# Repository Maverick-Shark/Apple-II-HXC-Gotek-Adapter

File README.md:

### Source

https://github.com/liveboxandy/Gotek-Rotary-Encoder

###  Description

Simple adapter PCB based on the wiring diagram from https://hxc2001.com/docs/gotek-floppy-emulator-hxc-firmware/pages/apple.html

### BOM

[Interactive BOM](https://djtersteegc.github.io/Apple-II-HXC-Gotek-Adapter/ibom.html)

| Item                                | Qty  | Notes                               | Link                                                         |
| ----------------------------------- | ---- | ----------------------------------- | ------------------------------------------------------------ |
| 2x17 34p 2.54mm Female Pin Socket   | 1    |                                     | [AliExpress](https://www.aliexpress.us/item/3256805948524386.html) |
| 2x10 20p 2.54mm IDC Male Box Header | 1    |                                     | [AliExpress](https://www.aliexpress.us/item/3256807284267150.html) |
| 1x4 4p 2.54mm Female Pin Socket     | 1    |                                     | [AliExpress](https://www.aliexpress.us/item/2255800509919410.html) |
| Female Dupont Jumper Wires          | 2    | From adapter to Gotek TX/RX headers | [AliExpress](https://www.aliexpress.us/item/3256807188673626.html) |
| 1x40 2.54mm Male Header             | 1    | To populate Gotek header pins       | [AliExpress](https://www.aliexpress.us/item/3256805949945647.html) |

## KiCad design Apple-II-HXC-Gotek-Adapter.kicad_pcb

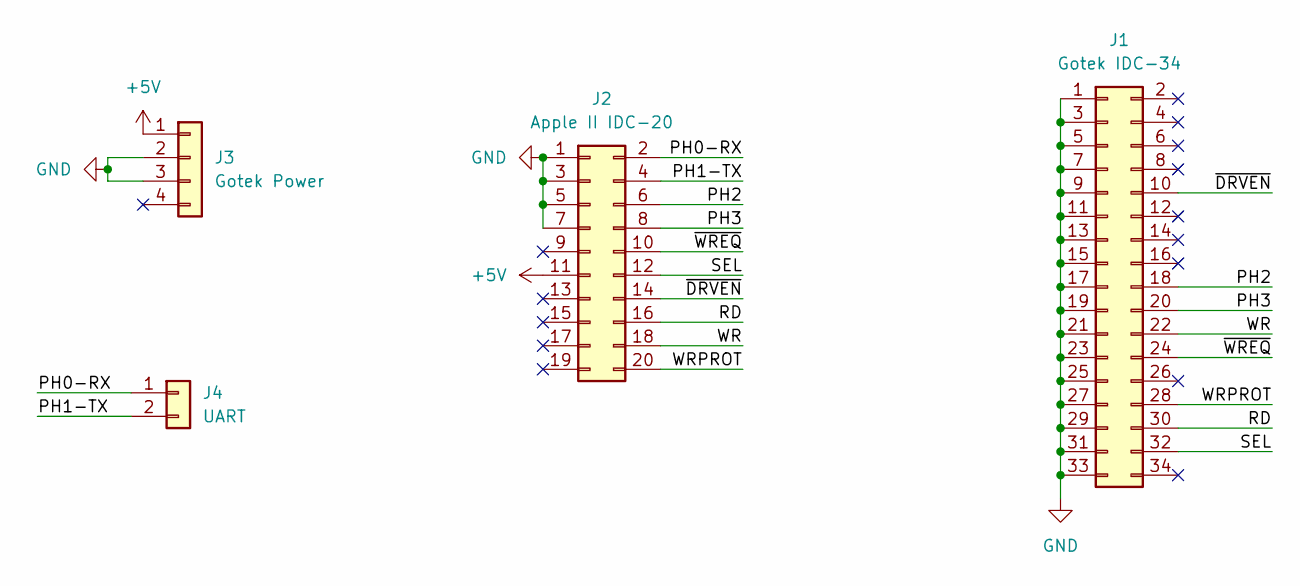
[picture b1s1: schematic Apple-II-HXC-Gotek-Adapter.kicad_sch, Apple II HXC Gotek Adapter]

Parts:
J1: Gotek IDC-34; PinSocket_2x17_P2.54mm_Vertical
J2: Apple II IDC-20; IDC-Header_2x10_P2.54mm_Vertical
J3: Gotek Power; PinSocket_1x04_P2.54mm_Vertical
J4: UART; PinHeader_2x01_P2.54mm_Vertical

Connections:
+5V: J2.11, J3.1
/PH0-RX: J2.2, J4.1
/PH1-TX: J2.4, J4.2
/PH2: J1.18, J2.6
/PH3: J1.20, J2.8
/RD: J1.30, J2.16
/SEL: J1.32, J2.12
/WR: J1.22, J2.18
/WRPROT: J1.28, J2.20
/~DRVEN: J1.10, J2.14
/~WREQ: J1.24, J2.10
GND: J1.1, J1.3, J1.5, J1.7, J1.9, J1.11, J1.13, J1.15, J1.17, J1.19, J1.21, J1.23, J1.25, J1.27, J1.29, J1.31, J1.33, J2.1, J2.3, J2.5, J2.7, J3.2, J3.3

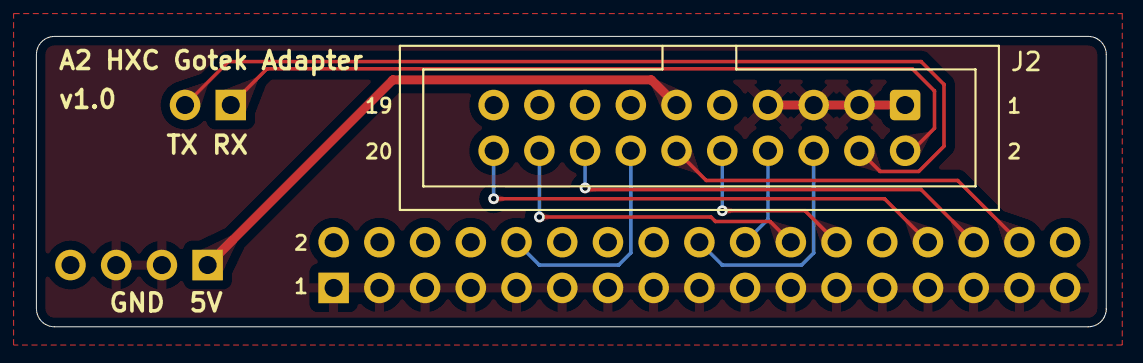
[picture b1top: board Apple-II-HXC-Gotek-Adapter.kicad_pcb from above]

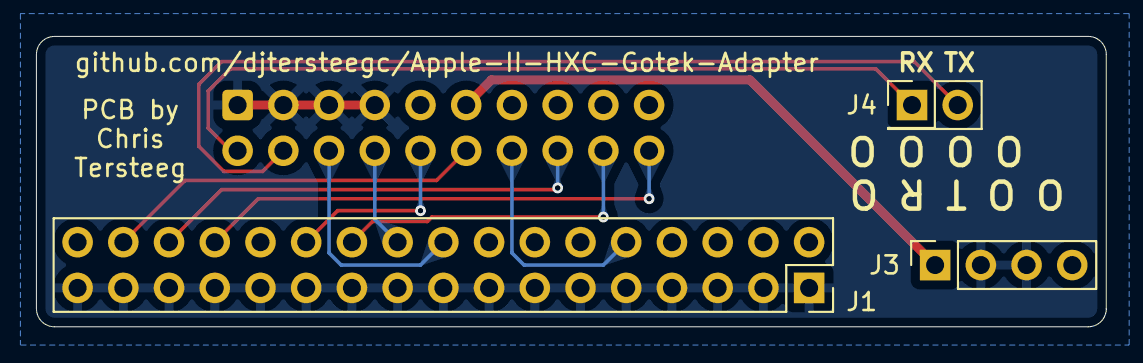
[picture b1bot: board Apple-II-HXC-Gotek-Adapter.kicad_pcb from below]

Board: 2 copper layers, 59.4 x 16.1 mm, 4 parts (3 on the bottom side), 12 nets.

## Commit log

2024-12-16 v1.0
2024-12-16 Add pics
2024-12-16 Add BOM
2025-08-31 Update README.md
    Source link added
